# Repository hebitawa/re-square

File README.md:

# re-square

Re:Square is a custom DIY split keyboard.

This repository contains schematics, firmware, and related design files.

Work in progress.

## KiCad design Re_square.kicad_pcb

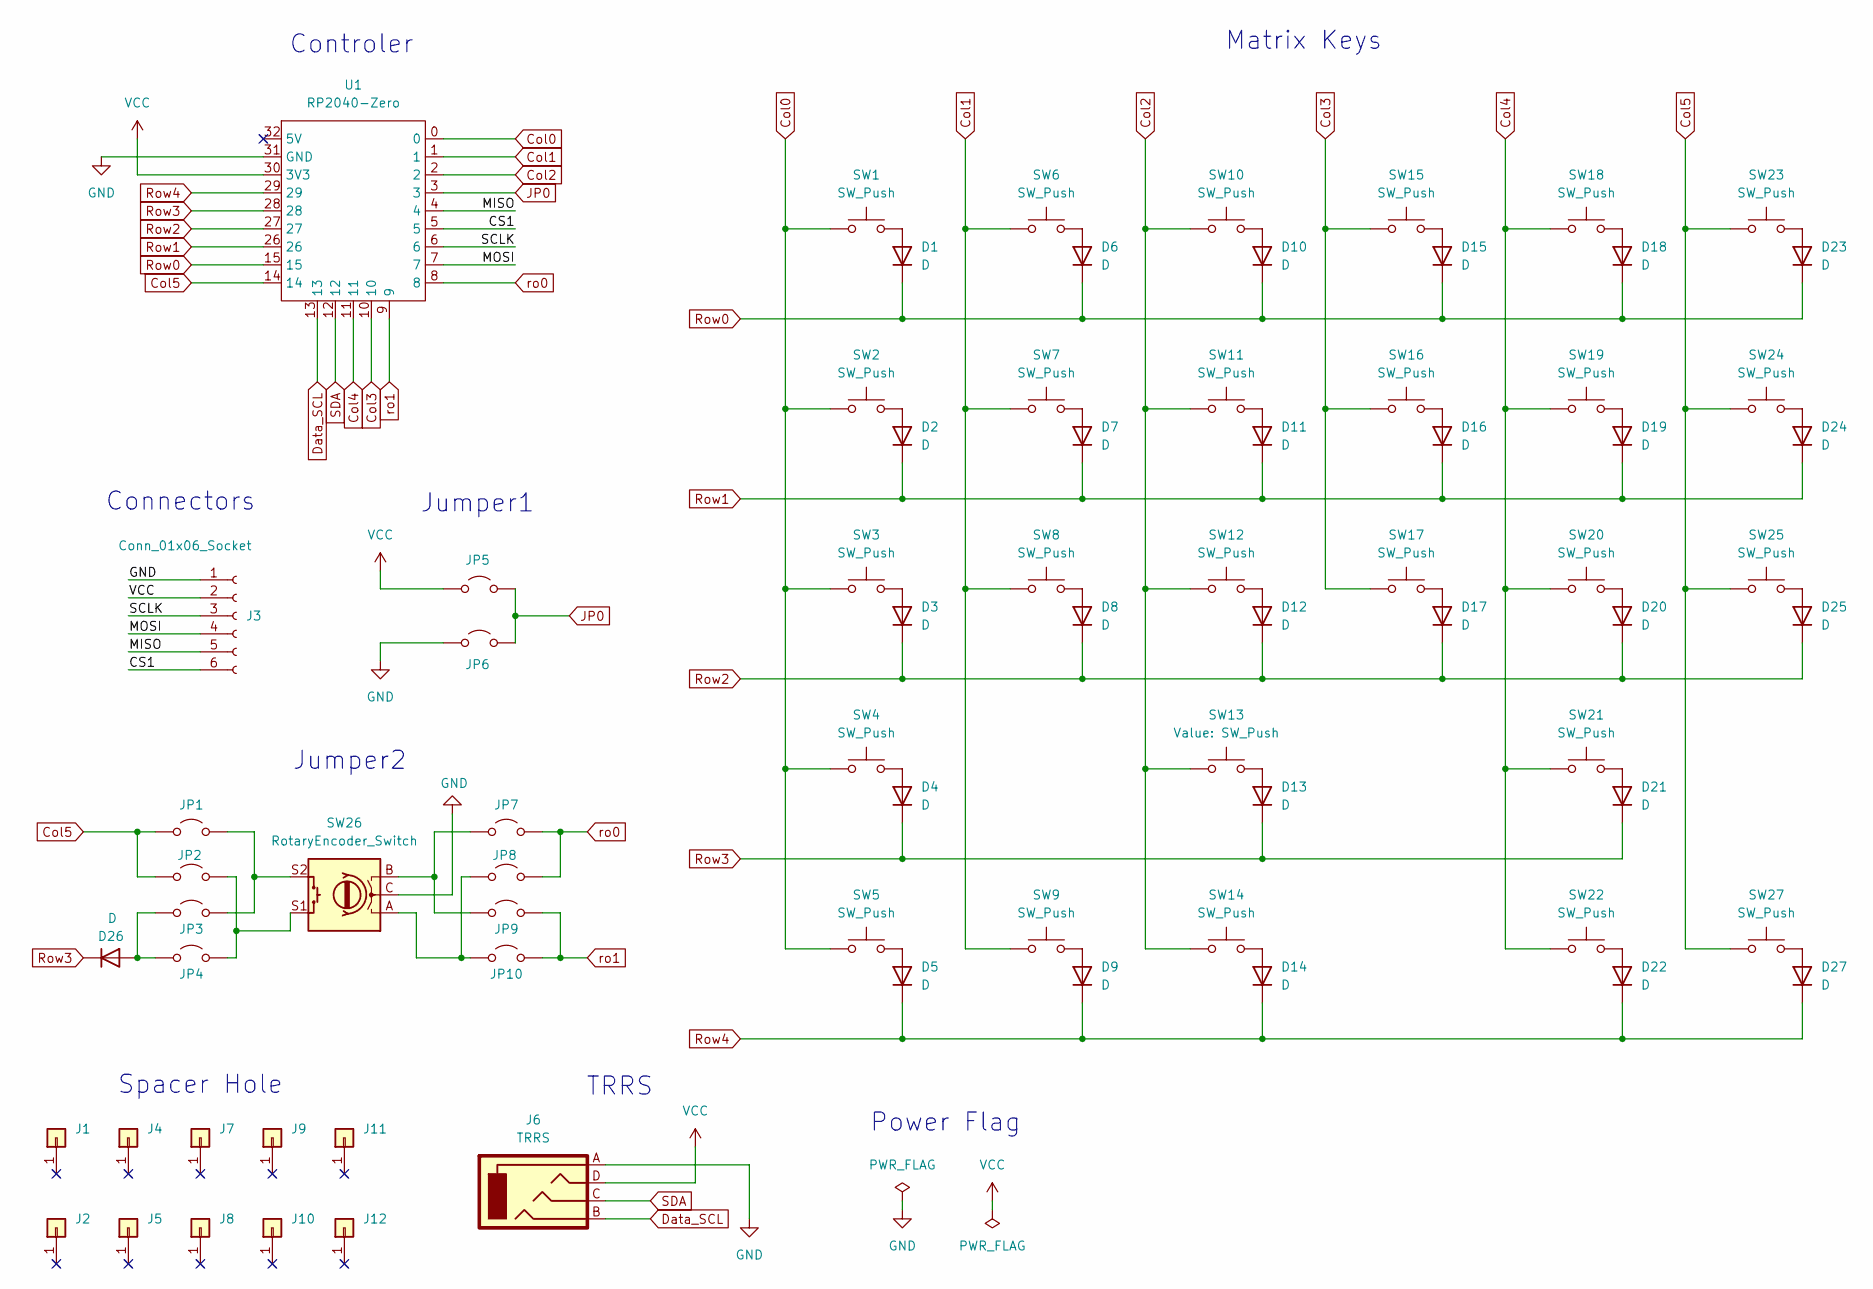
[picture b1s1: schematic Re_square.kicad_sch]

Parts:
D1, D2, D3, D4, D5, D6, D7, D8, D9, D10, D11, D12, D13, D14, D15, D16, D17, D18, D19, D20, D21, D22, D23, D24, D25, D26, D27: D; Diode_SMD_Rev
J1, J2, J4, J5, J7, J8, J9, J10, J11, J12: Conn_01x01; m2_Spacer_Hole
J3: Conn_01x06_Socket; PinHeader_1x06_P2.00mm_Vertical
J6: TRRS; TRRS_MJ-4PP-9
JP1, JP2, JP3, JP4, JP5, JP6, JP7, JP8, JP9, JP10: Jumper_2_Open; SolderJumper-2_P1.3mm_Open_TrianglePad1.0x1.5mm
SW1, SW2, SW3, SW5, SW6, SW7, SW8, SW9, SW10, SW11, SW12, SW13, SW14, SW15, SW16, SW17, SW18, SW19, SW20, SW22, SW23, SW24, SW25, SW27: SW_Push; CherryMX_Hotswap_1u_rev
SW4, SW21: SW_Push; CherryMX_Hotswap_2u_rev
SW26: RotaryEncoder_Switch; keyswitch_cherrymx_hotswap_1u_rotary_encoder_ec12
U1: RP2040-Zero

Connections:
/CS1: J3.6, U1.5
/MISO: J3.5, U1.4
/MOSI: J3.4, U1.7
/SCLK: J3.3, U1.6
Col0: SW1.1, SW2.1, SW3.1, SW4.1, SW5.1, U1.0
Col1: SW6.1, SW7.1, SW8.1, SW9.1, U1.1
Col2: SW10.1, SW11.1, SW12.1, SW13.1, SW14.1, U1.2
Col3: SW15.1, SW16.1, SW17.1, U1.10
Col4: SW18.1, SW19.1, SW20.1, SW21.1, SW22.1, U1.11
Col5: JP1.1 (A), JP2.1 (A), SW23.1, SW24.1, SW25.1, SW27.1, U1.14
Data_SCL: J6.B, U1.13
GND: J3.1, J6.A, JP6.1 (A), SW26.C, U1.31 (GND)
JP0: JP5.2 (B), JP6.2 (B), U1.3
unnamed: D1.2 (A), SW1.2
unnamed: D2.2 (A), SW2.2
unnamed: D3.2 (A), SW3.2
unnamed: D4.2 (A), SW4.2
unnamed: D5.2 (A), SW5.2
unnamed: D6.2 (A), SW6.2
unnamed: D7.2 (A), SW7.2
unnamed: D8.2 (A), SW8.2
unnamed: D9.2 (A), SW9.2
unnamed: D10.2 (A), SW10.2
unnamed: D11.2 (A), SW11.2
unnamed: D12.2 (A), SW12.2
unnamed: D13.2 (A), SW13.2
unnamed: D14.2 (A), SW14.2
unnamed: D15.2 (A), SW15.2
unnamed: D16.2 (A), SW16.2
unnamed: D17.2 (A), SW17.2
unnamed: D18.2 (A), SW18.2
unnamed: D19.2 (A), SW19.2
unnamed: D20.2 (A), SW20.2
unnamed: D21.2 (A), SW21.2
unnamed: D22.2 (A), SW22.2
unnamed: D23.2 (A), SW23.2
unnamed: D24.2 (A), SW24.2
unnamed: D25.2 (A), SW25.2
unnamed: D26.2 (A), JP3.1 (A), JP4.1 (A)
unnamed: D27.2 (A), SW27.2
unnamed: JP1.2 (B), JP3.2 (B), SW26.S2
unnamed: JP2.2 (B), JP4.2 (B), SW26.S1
unnamed: JP7.1 (A), JP9.1 (A), SW26.B
unnamed: JP8.1 (A), JP10.1 (A), SW26.A
Row0: D1.1 (K), D6.1 (K), D10.1 (K), D15.1 (K), D18.1 (K), D23.1 (K), U1.15
Row1: D2.1 (K), D7.1 (K), D11.1 (K), D16.1 (K), D19.1 (K), D24.1 (K), U1.26
Row2: D3.1 (K), D8.1 (K), D12.1 (K), D17.1 (K), D20.1 (K), D25.1 (K), U1.27
Row3: D4.1 (K), D13.1 (K), D21.1 (K), D26.1 (K), U1.28
Row4: D5.1 (K), D9.1 (K), D14.1 (K), D22.1 (K), D27.1 (K), U1.29
SDA: J6.C, U1.12
VCC: J3.2, J6.D, JP5.1 (A), U1.30 (3V3)
ro0: JP7.2 (B), JP8.2 (B), U1.8
ro1: JP9.2 (B), JP10.2 (B), U1.9

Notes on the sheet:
Matrix Keys
Connectors
Power Flag
Jumper2
Spacer Hole
Jumper1
TRRS
Controler

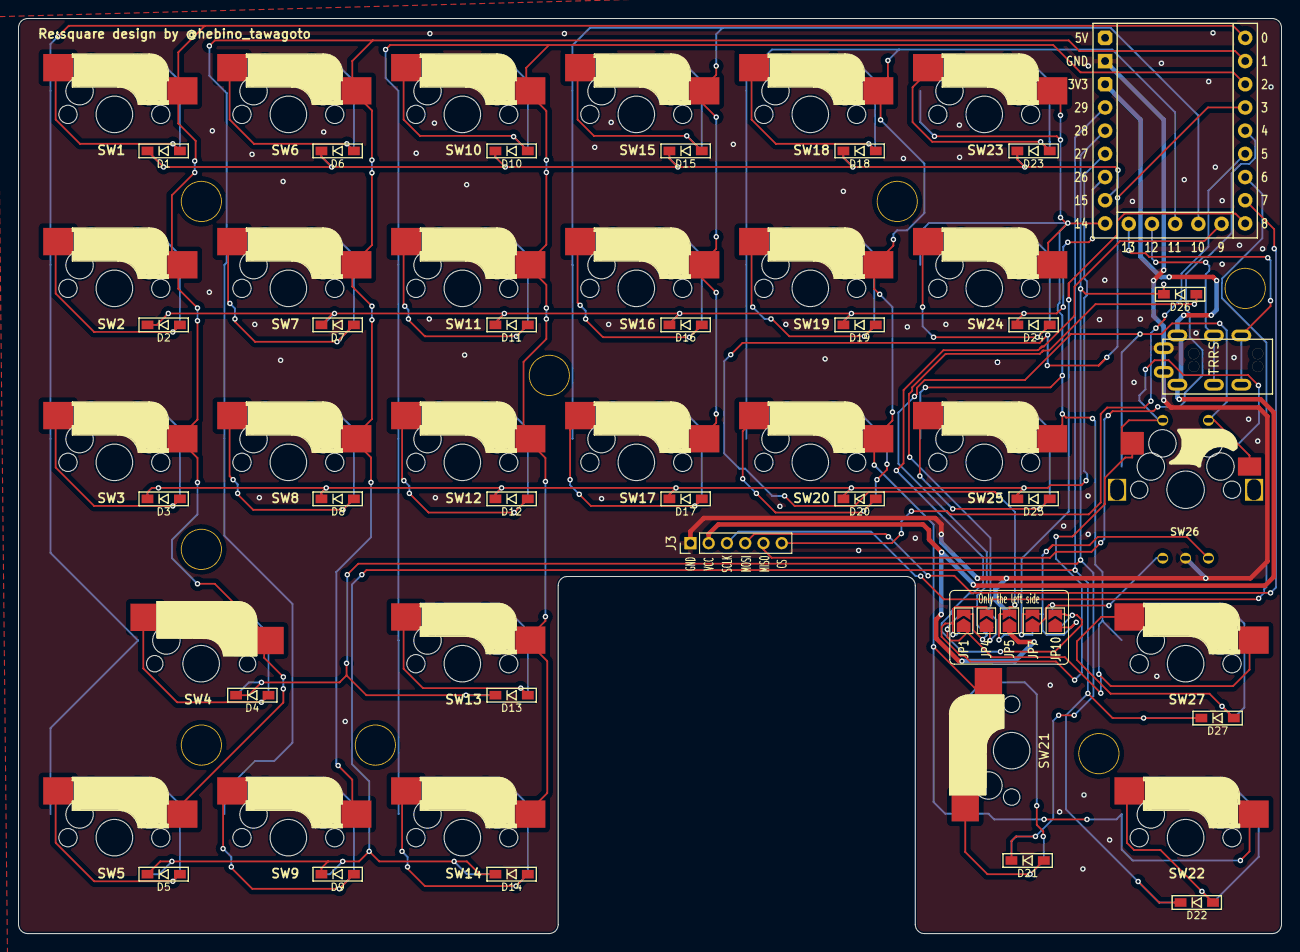
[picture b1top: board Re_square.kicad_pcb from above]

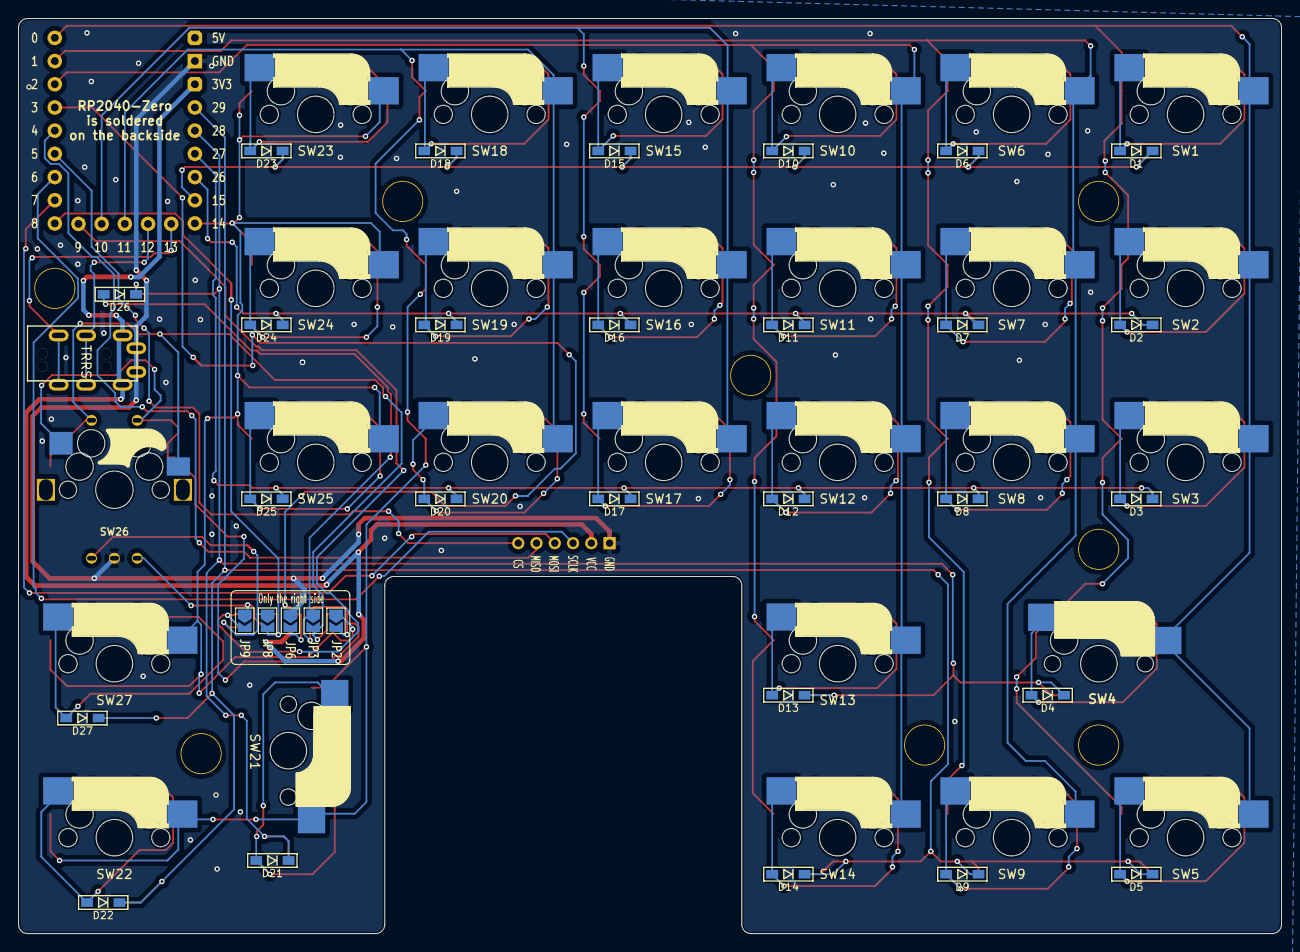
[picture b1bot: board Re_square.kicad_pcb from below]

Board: 2 copper layers, 138.3 x 100.2 mm, 75 parts (5 on the bottom side), 53 nets.

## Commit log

2026-03-01 Create test
